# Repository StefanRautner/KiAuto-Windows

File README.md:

KiAuto
======
KiCad automation scripts.
In particular to automate tasks that can't be done using the KiCad native Python interface.
The automation is carried out emulating the user interaction.

## Index

* [Introduction](#introduction)
* [Installation](#installation)
  * [Dependencies](#dependencies)
  * [No installation](#no-installation)
  * [Installation using pip](#installation-using-pip)
  * [Python style installation](#python-style-installation)
  * [Installation on Ubuntu/Debian](#installation-on-debian)
* [Usage](#usage)
  * [Export a schematic to PDF or SVG](#export-a-schematic-to-pdf-or-svg)
  * [Run ERC](#run-erc)
  * [Generate netlist](#generate-netlist)
  * [Update BoM XML or basic BoM generation](#update-bom-xml-or-basic-bom-generation)
  * [Run DRC](#run-drc)
  * [Export layout as PDF](#export-layout-as-pdf)
  * [Refilling copper zones](#refilling-copper-zones)
  * [Common options](#common-options)
  * [Ignoring warnings and errors from ERC or DRC](#ignoring-warnings-and-errors-from-erc-or-drc)
  * [Running on GitLab CI](#running-on-gitlab-ci)
* [History](#history)

## Introduction

Current implementation uses a virtual X server ([xvfb](https://www.x.org/releases/X11R7.6/doc/man/man1/Xvfb.1.xhtml)),
sends key events and detects which window is focused using [xdotool](https://github.com/jordansissel/xdotool/).
This means it works for Linux. KiCad is also available for Windows and MacOSX, help to port the scripts will be appreciated.

Currently tested and working:

- Exporting schematics to PDF, SVG, PS, DXF and HPGL
- Exporting layouts (PCBs) to PDF
- Running ERC on schematics
- Running DRC on layouts
- Netlist generation (including IPC-D-356 format)
- Basic BoM generation (mainly the XML needed for [KiBoM](https://github.com/SchrodingersGat/KiBoM))
- PCB 3D render
- Export PCB in Gencad format
- Export PCB in VRML format

If you are looking for Gerbers, Drill, Position, STEP and more take a look at [KiBot](https://github.com/INTI-CMNB/KiBot).

This project started as a fork of [kicad-automation-scripts](https://github.com/obra/kicad-automation-scripts) for more information read the [history](#History) section.

A docker image containg the scripts and other tools can be found at [DockerHub](https://hub.docker.com/repository/docker/setsoft/kicad_auto).

## Installation

### Dependencies

If you are installing from a Debian package you don't need to worry about dependencies, otherwise you need to install:

- **Python 3.4** or newer
- [**KiCad**](http://kicad.org/) 5.1.x or newer, KiCad 6.x is supported
- [**Xvfb**](https://www.x.org/releases/X11R7.6/doc/man/man1/Xvfb.1.xhtml) This is the X Virtual Frame Buffer, part of X, but usually available as a separated package (i.e. `xvfb`)
- [**xdotool**](https://github.com/jordansissel/xdotool)
- [**xsltproc**](http://xmlsoft.org/xslt/) (usually installed as a KiCad dependency). Only needed for BoMs.
- [**import**](https://imagemagick.org/) from Image Magick. Also provided by Graphics Magick. Only needed for ERC with KiCad 6.
- [**xclip**](https://github.com/astrand/xclip). Only needed by kicad2step_do when using KiCad 6.

The following Python modules are also needed, they are installed by the Debian package and `pip`:

- [**xvfbwrapper**](https://pypi.org/project/xvfbwrapper/)
- [**psutil**](https://pypi.org/project/psutil/)

If you want to debug problems you could also need:

- [**recordmydesktop**](http://recordmydesktop.sourceforge.net/about.php), to create a video of the KiCad session.
- [**x11vnc**](http://www.karlrunge.com/x11vnc/) and a client like [**ssvnc**](http://www.karlrunge.com/x11vnc/ssvnc.html), to see the KiCad live interaction.
- [**fluxbox**](http://fluxbox.org/) and [**wmctrl**](http://tripie.sweb.cz/utils/wmctrl/) if you want to have a window manager when using **x11vnc**. Othewise windows can't be moved.

### Installation using pip

```shell
pip3 install kiauto
```

Note: the `pip` command is usually installed as `pip3` on modern systems. To avoid confusing it with Python 2 version.
You can also install the current git code running:

```shell
pip3 install .
```

In the root of the repo.

### Python style installation

Just run the setup, like with any other Python tool:

```
sudo python3 setup.py install
```

### No installation

You can use the scripts without installing. The scripts are located at the *src/* directory.

You can also define bash aliases:

```
alias pcbnew_do=PATH_TO_REPO/src/pcbnew_do
alias eeschema_do=PATH_TO_REPO/src/eeschema_do
```

Note that the following Python 3 packages must be installed:

- [**xvfbwrapper**](https://pypi.org/project/xvfbwrapper/)
- [**psutil**](https://pypi.org/project/psutil/)

Also note that this won't work if you plan to call the scripts from KiBot or other tool.
Aliases are good for direct command line use, but are restricted to the shell where the aliases are declared.
You can add the aliases to the bash configuration, but if the tool doesn't use bash or don't even use a shell this won't work.

### Installation on Debian

Get the Debian package from the [releases section](https://github.com/INTI-CMNB/KiAuto/releases) and run:
```
sudo apt install ./kiauto_*_all.deb
```

## Usage

Two scripts are provided:

- **eeschema_do**: interacts with KiCad's eeschema (schematic editor)
- **pcbnew_do**: interacts with KiCad's pcbnew (PCB editor)

You can get detailed help using the *--help* command line option. Here I include some basic usage.

### Export a schematic to PDF or SVG

```
eeschema_do export -a YOUR_SCHEMATIC.sch DESTINATION/
```
This will create *DESTINATION/YOUR_SCHEMATIC.pdf* file containing all the schematic pages. If you want just one page remove the *-a* option. If you want an SVG file just use *-f svg* like this:
```
eeschema_do export -a -f svg YOUR_SCHEMATIC.sch DESTINATION/
```
In this case you'll get one SVG for each page in your schematic.

### Run ERC

To run the Electrical Rules Check:
```
eeschema_do run_erc YOUR_SCHEMATIC.sch DESTINATION/
```
If an error is detected you'll get a message and the script will return a negative error level. Additionally you'll get *DESTINATION/YOUR_SCHEMATIC.erc* containing KiCad's report.

### Generate netlist

To generate or update the netlist, needed by other tools:
``` 
eeschema_do netlist YOUR_SCHEMATIC.sch DESTINATION/
```
You'll get *DESTINATION/YOUR_SCHEMATIC.net*

### Update BoM XML or basic BoM generation:

Tools like [KiBoM](https://github.com/SchrodingersGat/KiBoM) can generate a nice BoM, but in order to run them from the command line you need to be sure that the project's XML BoM is updated. You can do it running:
``` 
eeschema_do bom_xml YOUR_SCHEMATIC.sch DESTINATION/
```
After running it *./YOUR_SCHEMATIC.xml* will be updated.

### Run DRC

To run the Distance Rules Check:
```
pcbnew_do run_drc YOUR_PCB.kicad_pcb DESTINATION/
```
If an error is detected you'll get a message and the script will return a negative error level. Additionally you'll get *DESTINATION/drc_result.rpt* containing KiCad's report. You can select the name of the report using *--output_name* and you can ignore unconneted nets using *--ignore_unconnected*.

### Export layout as PDF

This is useful to complement your gerber files including some extra information in the *Dwgs.User* or *Cmts.User* layer.
```
pcbnew_do export YOUR_PCB.kicad_pcb DESTINATION/ LAYER1 LAYER2
```
Will generate *DESTINATION/printed.pdf* containing LAYER1 and LAYER2 overlapped. You can list as many layers as you want. I use things like ```F.Cu Dwgs.User```. The name of the layers is the same you see in the GUI, if your first inner layer is GND you just need to use ```GND.Cu```.

If you need to get a list of valid layers run:

```
pcbnew_do export --list YOUR_PCB.kicad_pcb
```

### Refilling copper zones

When you run the DRC KiCad will refill all zones. If you didn't do it before saving it could lead to a situation where the PCB that passes DRC isn't the one saved to disk. To solve you can use *-s* option to save the PCB after DRC:

```
pcbnew_do run_drc -s YOUR_PCB.kicad_pcb DESTINATION/
```

Another option could be to avoid changing the file on disk, but fill the zones before printing. To achieve it you can invoke the export command like this:

```
pcbnew_do export -f YOUR_PCB.kicad_pcb DESTINATION/ LAYERs...
```

### Common options

By default all the scripts run very quiet. If you want to get some information about what's going on use *-v*. 

The nature of these scripts make them very fragile. In particular when you run them in your every day desktop. You must avoid having *eeschema* and/or *pcbnew* windows opened while running the scripts. If you need to debug a problem you can:
1. Use the *-vv* option to get debug information
2. Use the *-r* option to record a video (OGV format) containing the GUI session. The file will be stored in the output directory and its name will begin with the name of the requested command.
3. Use the *-s* and *-w* options to start **x11vnc**. The execution will stop asking for a keypress. At this time you can start a VNC client like this: ```ssvncviewer :0```. You'll be able to see KiCad running and also interact with it.
4. Same as 3 but also using *-m*, in this case you'll get a window manager to move the windows and other stuff.

### Ignoring warnings and errors from ERC or DRC

Sometimes we need to ignore some warnings and/or errors reported during the ERC and/or DRC test.

To achieve it you need to create a *filters file*. Each line contains a rule to exclude one or more matching errors. The syntax is:

```
ERROR_ID,REGULAR_EXPRESSION
```

The regular expression must follow the Python syntax. In the simplest case this can be just the text that the error must contain.

The error id is just the KiCad internal number for the error you want to ignore. For KiCad 6 this is a string, not a number.

Here is an example, suppose our report says:

```
** Created on 2020-06-05 11:16:21 **

** Found 2 DRC errors **
ErrType(45): Courtyards overlap
    @(144.361 mm, 101.752 mm): Footprint C16 on F.Cu
    @(144.825 mm, 101.244 mm): Footprint C19 on F.Cu
ErrType(45): Courtyards overlap
    @(159.885 mm, 97.663 mm): Footprint R4 on F.Cu
    @(160.393 mm, 97.191 mm): Footprint C21 on F.Cu

** Found 0 unconnected pads **

** End of Report **
```

Here we have two errors, both number 45. So lets suppose we want to ignore the first error, we could use the following filter:

```
45,Footprint C16
```

This will ignore any error of type 45 (Courtyards overlap) related to *Footprint C16*. To use
it you just need mto use the *-f* command line option:

```
pcbnew_do run_drc -f FILTER_FILE YOUR_PCB.kicad_pcb DESTINATION/
```

Note that when using KiCad 6 the errors are strings enclosed by brackets, use only the text, not the brackets.

### Running on GitLab CI

If you want to use KiAuto in GitLab CI servers I'll recommend always using the `-r` option.

The scripts runs very well locally and using GitHub CI servers.
It also worked well on april 25 2020 on GitLab CI.
Tests on august 25 2020 on GitLab CI started to fail.
The v1.5.8 implements a workaround that is working on february 22 2021, but you must enable recording.

In case you are interested the misterious problem is related with the use Xvfb.
After starting Xvfb process we start polling it to ensure the server is up and running.
We use the `setxkbmap -query` command to know if Xvfb finished its start-up and is working.
After we can successfully run `setxkbmap -query` we assume Xvfb is fully functional.
For some reason this isn't true on GitLab CI servers, if we don't wait some time after the test the X server doesn't respond.
What is even more misterious is that we must run `recordmydesktop` or KiCad will fail to initialize GTK+.
I don't have any idea of why, but it works.

## History

I saw a presentation of Jesse Vincent ([@obra](https://github.com/obra)) in the [KiCon 2019](https://2019.kicad-kicon.com/) about automating KiCad tasks.

The presentation used [kicad-automation-scripts](https://github.com/obra/kicad-automation-scripts) as base for the tasks that needs to emulate the user interaction.
So I forked this repo.

But this wasn't the original repo, Jesse's repo is a fork of Productize SPRL's [scripts](https://github.com/productize/kicad-automation-scripts).
These scripts were created by Seppe Stas ([@seppestas](https://github.com/seppestas)).

According to Seppe he took many ideas from the [split-flap display project](https://scottbez1.github.io/splitflap/).
In particular from the files [here](https://github.com/scottbez1/splitflap/tree/master/electronics/scripts).
The author of split-flap is Scott Bezek ([@scottbez1](https://github.com/scottbez1)).
Scott explained the idea in his [blog](https://scottbezek.blogspot.be/2016/04/scripting-kicad-pcbnew-exports.html)

So this is the history of the scripts, at least what I know. In short: Scott Bezek had the original idea and used it for his project, but not as a separated tool.
Seppe Stas from Productize SPRL took the scripts and created a tool from them.
Then Jesse Vincent used the scripts to create a bigger set of tools and presented it on KiCon 2019.
Then Salvador E. Tropea took Jesse's scripts and adapted them to the needs of [KiBot](https://github.com/INTI-CMNB/KiBot).
And Finally I (Stefan Rautner) took the scripts and made a Version that is compatible with Windows.

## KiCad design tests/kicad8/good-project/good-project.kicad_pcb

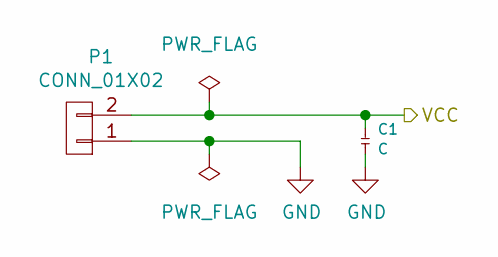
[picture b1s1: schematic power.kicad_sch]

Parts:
C1: C; C_0402_1005Metric
P1: CONN_01X02; JST_JWPF_B02B-JWPF-SK-R_1x02_P2.00mm_Vertical

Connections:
/Power/VCC: C1.1, P1.2; also elsewhere on the board
GND: C1.2, P1.1; also elsewhere on the board

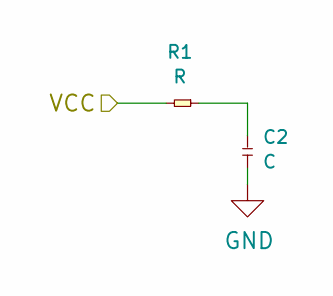
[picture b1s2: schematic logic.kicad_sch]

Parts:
C2: C; C_0402_1005Metric
R1: R; R_0402_1005Metric

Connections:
/Power/VCC: R1.1; also elsewhere on the board
GND: C2.2; also elsewhere on the board
unnamed: C2.1, R1.2

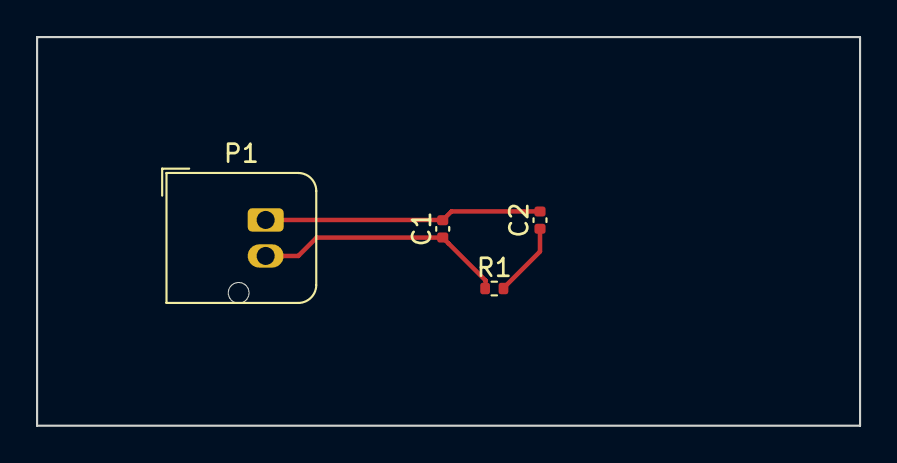
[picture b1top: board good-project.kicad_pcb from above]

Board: 6 copper layers, 45.7 x 21.6 mm, 4 parts (0 on the bottom side), 3 nets.

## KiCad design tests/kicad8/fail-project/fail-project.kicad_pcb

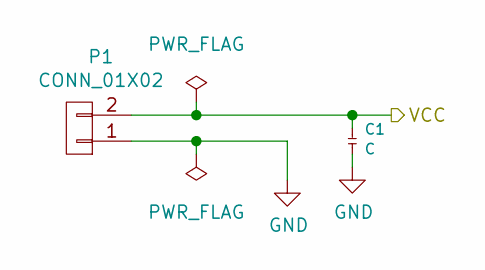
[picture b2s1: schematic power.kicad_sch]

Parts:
C1: C; C_0402_1005Metric
P1: CONN_01X02; JST_JWPF_B02B-JWPF-SK-R_1x02_P2.00mm_Vertical

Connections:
GND: C1.2, P1.1; also elsewhere on the board
VCC: C1.1, P1.2; also elsewhere on the board

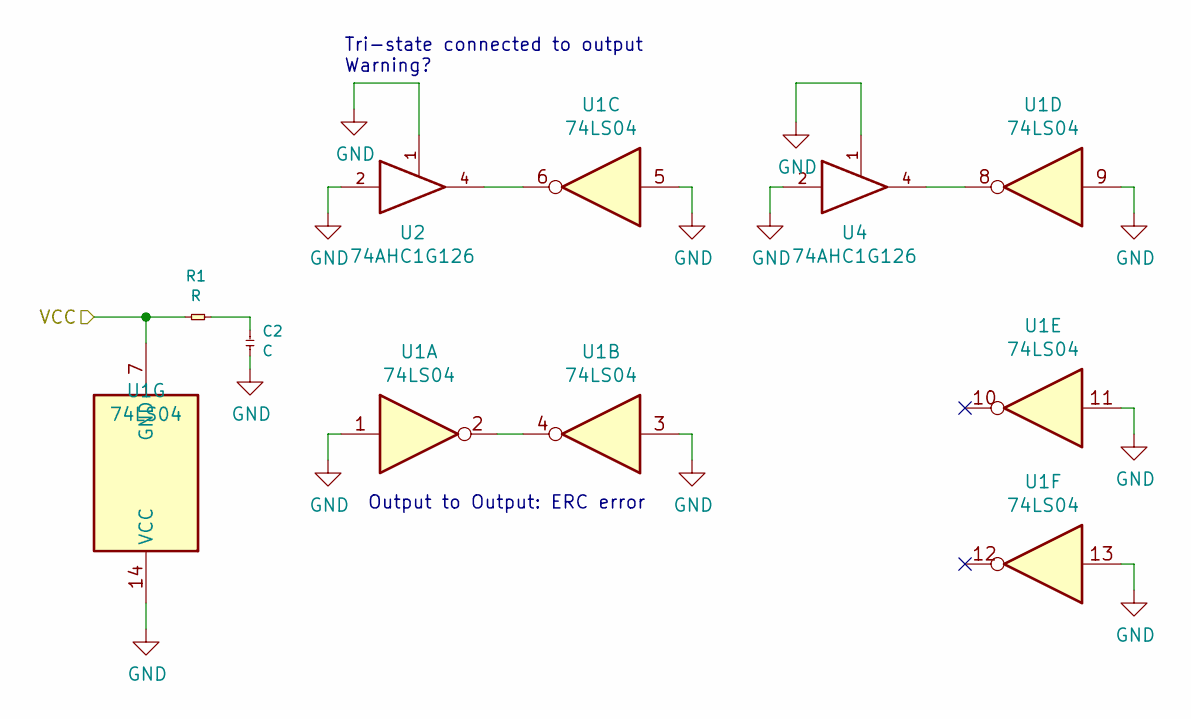
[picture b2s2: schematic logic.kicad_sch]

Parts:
C2: C; C_0402_1005Metric
R1: R; R_0402_1005Metric
U1: 74LS04
U2, U4: 74AHC1G126

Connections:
GND: C2.2, U1.1, U1.3, U1.5, U1.9, U1.11, U1.13, U1.14 (VCC), U2.1, U2.2, U2.3 (GND), U4.1, U4.2, U4.3 (GND); also elsewhere on the board
unnamed: C2.1, R1.2
unnamed: U1.2, U1.4
unnamed: U1.6, U2.4
unnamed: U1.8, U4.4
VCC: R1.1, U1.7 (GND), U2.5 (VCC), U4.5 (VCC); also elsewhere on the board

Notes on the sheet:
Tri-state connected to output Warning?
Output to Output: ERC error

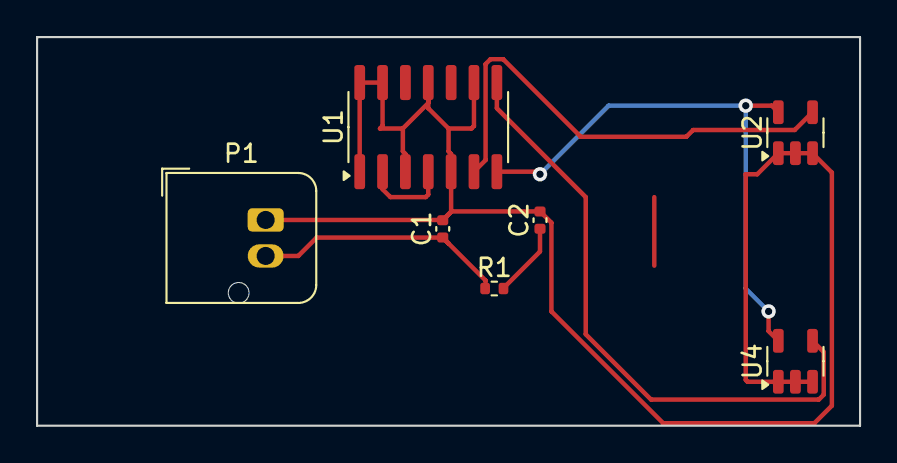
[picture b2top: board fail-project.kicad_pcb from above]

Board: 2 copper layers, 45.7 x 21.6 mm, 7 parts (0 on the bottom side), 6 nets.

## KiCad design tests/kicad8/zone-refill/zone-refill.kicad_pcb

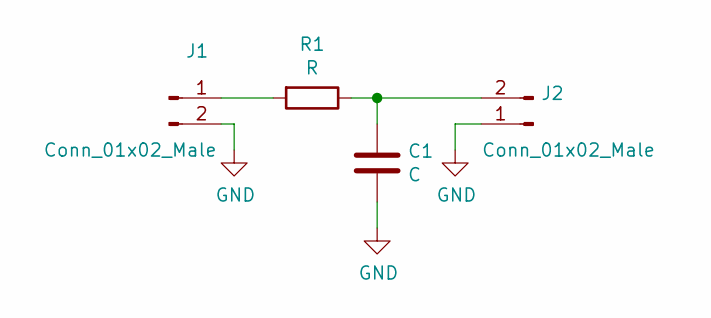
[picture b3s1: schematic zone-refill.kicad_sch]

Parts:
C1: C; C_0805_2012Metric
J1, J2: Conn_01x02_Male; PinHeader_1x02_P2.54mm_Vertical
R1: R; R_0805_2012Metric

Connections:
GND: C1.2, J1.2, J2.1
unnamed: J1.1, R1.2
unnamed: C1.1, J2.2, R1.1

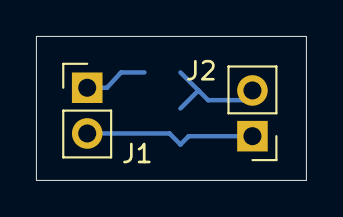
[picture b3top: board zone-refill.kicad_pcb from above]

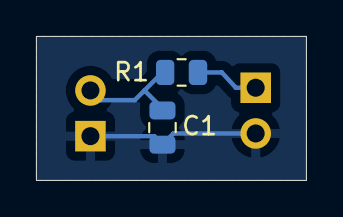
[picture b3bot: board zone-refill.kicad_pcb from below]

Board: 2 copper layers, 15.0 x 8.0 mm, 4 parts (2 on the bottom side), 3 nets.

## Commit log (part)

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2022-10-11 Bumped version to 2.0.6
2022-12-17 Added some preliminar VRML export support
2022-12-17 [Export VRML] Added KiCad 5 support
2022-12-17 [Export VRML] Added some basic tests
    - The file are there ;-)
2022-12-17 Updated changelog
2022-12-17 [CI/CD] Migrated to checkout v3
2022-12-17 Bumped version to 2.1.0
2023-01-11 [Eeschema][Export] Added new options
    - Color theme
    - Enable background color
    - HPGL origin
    - HPGL pen size
    Related to INTI-CMNB/KiBot#362
2023-01-11 [DOCs] Fixed README badge
2023-02-06 [DOCs][Fixed] We no longer generate a CSV as an xml_update side effect
2023-02-07 [ERC] KiCad 7 support
2023-02-07 [Netlist] KiCad 7 support
    - First use of kicad-cli
2023-02-07 [BOM_XML] KiCad 7 support
2023-02-07 [Export] KiCad 7 support
    - All eeschema_do outputs now supports KiCad 7
2023-02-07 [EEschema Export][KiCad 7] Now using the CLI when possible
2023-02-07 [Export GenCAD] KiCad 7 support
    - Works out-of-the-box
2023-02-07 [PCBNew Export] KiCad 7 support
    - Just a small dialog change
2023-02-07 [PCBNew Export] Added note about KiCad 7 bug
2023-02-07 [Render_3D] Added KiCad 7 references
2023-02-08 Replacd nightly version
2023-02-08 [Flake8] Fixed details
2023-02-08 [Interposer] Added support for async dialogs during text paste
2023-02-08 [DRC] KiCad 7 support
    - Python workaround for missing environment variable and fp-lib-table
    Related to a new check for libs
    - New dialog name
    - Adapted the test cases for the new tests
2023-02-08 Fixed missing import symbol
2023-02-08 Fixed flake8 issues
2023-02-08 Fixed 3D models
    - Lost during footprint update done to fix DRC errors
2023-02-08 Adjusted GenCAD reference to KiCad 7 footprints
2023-02-08 Adjusted the references to the KiCad 7 footprints
2023-02-08 Disabled lib_footprint_mismatch (useless)
2023-02-08 Added KiCad 7 support when no interposer is available
2023-02-08 [Iterposer] Avoid waiting for a dialog that is already closed
2023-02-08 [Tests] Trying to enable "nightly" tests
2023-02-08 [Tests] Added missing KiCad 7 "missing-project" files
2023-02-08 Disabling CPU usage detection for KiCad 7, is failing
2023-02-09 Fixed CPU usage detection for nightly
    - It is run from a script, so we need to search for the child
2023-02-14 [Debian] Updated version
2023-02-14 [DOCs] Updated the changelog
2023-02-27 [ERC][Added] Option to select the grid size used for checks
2023-02-27 Bumped version to 2.2.1
2023-02-27 [Tests][Fixed] KiCad version detection
2023-02-27 [Tests] Adjusted the references now that KiCad 7 is fixed
    - Centered scaled print is now working
2023-02-27 [Tests][3D][KiCad 7] Adjusted references
    - Small changes in fonts, may be related to b2241dca72 patch
2023-02-27 Avoid problems when exiting and no interposer dialog
2023-02-27 [Tests][KiCad 7] Adapted references
    - All related to small changes in the font rendering
2023-03-06 Added workaround for KiKit 1.3.0 plugin
2023-03-19 Accept KiCad nightly as dependency
2023-04-02 [Makefile] Added target to run KiCad 7 using docker
2023-04-02 [EEschema] Added support for options in the v8 kicad-cli
2023-04-02 [Tests] Switching to test using KiCad 7 instead of nightly
2023-04-02 [DRC] Added workaround for KiCad 7 DRC API bug
    - No KICAD7* vars defined, KiBot does by itself
2023-04-02 [Makefile] Added local target for all Ki7 docker tests
2023-04-02 [KiCad 7] Updated references
2023-04-02 [Tests] Let the parallel jobs to finish if one fails.
2023-04-02 [Tests] Fixed faiñ-fast position
2023-04-02 [Tests] Trying without continu-on-error
2023-04-06 [Tests] Added auto save test files
2023-04-06 Added support for KICad async warnings
    - Missing font generates it
2023-04-06 Bumped version to 2.2.3
2023-04-12 Added better debug for global fp/sym-lib-table issues
2023-04-12 Added share directory detection
    - Also more consistent version flags
2023-04-12 [Eeschema_do][Added] Support for v7.99 ERC
    - Dialog not closed
    - File name forced by KiCad
2023-04-12 [KiCad 8][Added] Test and reference files
    - For 7.99
2023-04-12 [Tests][KiCad 7] Removed no longer needed fp-lib-table
    - 7.0.1 fixes it (7.99 don't)
2023-04-12 [Interposer][Added][KiCad 8] Support
    - ERC dialog not really closed
    - File names forced by KiCad
    - Async dialogs in send_keys (missing WKS)
2023-04-12 [Tests][Added] Targets to the Makefile
    - KiCad 7.99
2023-04-12 Bumped version to 2.2.4
2023-04-17 [Tests][good][KiCad 7] Adapted to the new ERC errors in 7.0.2
2023-04-17 [Eeschema][KiCad 7.0.2][Added] Workaround for ERC
    - Workaround for bogus KiCad 7.0.2 error about missing simulation model for
    power symbols.
2023-04-17 [Eeschema][KiCad 7.0.2][Added] Workaround for ERC dialog
    - Closes after running the ERC.
2023-04-17 [Eeschema] Better error/warning formating
2023-04-17 [Tests][KiCad 7] Ignore silk clipped by solder mask
2023-04-17 [Tests][References] Updated for the last changes
    - Mostly because I fixed some out-off-grid errors
2023-04-17 [Eeschema][ERC][KiCad 7][No interposer] Added workaround
2023-04-18 [Makefile] Switching to ki7 by default
2023-04-18 Bumped version to 2.2.5
2023-04-18 [3D] Added more delay to KiCad 5
2023-04-18 [KiCad2Step][Added] Support for the broken version in 7.99
    - The old --no-virtual was renamed to be more coherent, but breaking old code
    KiCad favors clarity over compatibility, and rarely both together.
2023-04-20 Changed shortcut for E/DRC
    - Ctrl+Shift+I is interpreted as Ctrl+Shift+^I, which is Ctrl+Shift+Tab,
    which is reserved by KiCad.
2023-04-20 [ERC] Added another 7.99 workaround
    - This dialog is crazy
2023-06-08 Bumped version to 2.2.6
    - Just to avoid confusion
2023-06-08 [Added][3d_view] More options to control the result
    - use_layer_colors: instead of realistic
    - hide_board_body: transparent core
    - show_comments: visible User.Comments (only when use_layer_colors enabled)
    - show_eco: visible Eco*.User (only when use_layer_colors enabled)
    - show_adhesive: visible *.Adhesive
    See INTI-CMNB/KiBot#445
2023-06-09 [Tests] KiCad 7.0.5 no longer specify the unit for an ERC error
    - So I made this filter more generic
2023-06-09 [Fixed] Problems with KiCad 7.0.5 ERC formatting
2023-06-09 [Tests][References][KiCad 7.0.5] Updated
2023-06-12 Updated docs for release
2023-08-08 Added support for KiCad 7.0.7 already opened dialog
    It adds more information about the user and host that locked the file
2023-08-08 Added support for KiCad 7.0.7 gencad dialog
    Without a Window Manager selecting the first checkbox and going up
    doesn't select the input text, the Browse button is selected.
2023-08-08 Added support for KiCad 7.0.7 ERC dialog behavior
    No longer closed by ESC, but we can use the patched button.
2023-08-08 Added stable nightly test
2023-08-08 Fixed stable nightly workflow deps
2023-08-08 Fixed stable nightly docker image name
2023-08-08 [Tests] Stable nightly test only manually triggered
    - Currently fails because of small details in KiCad PCB print
2023-08-08 [Tests] Updated the stable nightly used actions
2023-08-08 Bumped version to 2.2.7
2023-10-12 [Added][Experimental] Option to enable the file creation by PID
    When using the interposer.
    Related to INTI-CMNB/KiBot#367
2023-10-12 [Tests] Adjusted KiCad 7.0.8 references
2023-10-12 [Added] Support for KiCad 7.0.8 ERC details
2023-10-12 [Makefile][Added] Target for KiCad 6 + no interposer test
2023-10-12 [Tests][Added] More toletance to rendered images
2023-10-12 [ERC][Fixed] Error introduced in the 7.0.8 support
    Extra return
2023-10-12 [Fixed][KiCad 7.0.8] PCB print dialog
    When no interposer, the Print/Close buttons are moved
2023-10-12 [Fixed][KiCad 6][Eeschema][Plot] More robust
    Force buttons selection in a more robust way
2023-10-13 [Print][PCB][Fixed][No Interposer] Debian 12 issues
2023-10-13 [DRC][No Interposer][Fixed] Debian 12 issues
2023-10-22 [CI/CD] Build all images after a release
    But don't run the KiBot release tests, should be dev (not available)
2023-10-23 [Interposer] Look for architecture specific file
2023-11-02 [Fixed] Removed debug "error" from kicad2step_do
    Closes #34
2023-11-08 [Interposer][Experimental] Added fclose64 and close64
    - They doesn't exist on amd64, but perhaps they do on ARM64
2023-11-24 [flake8][Fixed] Small style details
2023-11-24 [Interposer] Compiled with Debian 11
    To make it compatible with KiCad 5
2023-11-24 Forced test
2024-02-02 [Tests] Adjusted GenCAD ref for KiCad 7.0.10
    The board edge is generated in the reverse order.
    Same result, different rotation of the points
2024-02-02 [Tests][CI/CD] Updated GitHub Actions versions
2024-02-09 [ERC][KiCad 8][Added] Support for CLI
    Lamentably affected by bugs, so still parsing text, which is even weaker
    because they removed the "Severity" keyword
2024-02-16 [Added][KiCad 8] Workaround for bogus lock message
2024-02-16 [PCBNew][DRC] Implemented CLI version
2024-02-16 [EEschema][ERC] Implemented kicad-cli JSON parser
2024-02-16 [PCBNew][DRC][Added][KiCad 8] More options
    - '--schematic-parity'/'-p' Check PCB vs SCH parity
    - '--all-track-errors'/'-t' Report all errors for each track
    - '--units'/'-u' Report units
2024-02-17 [KiCad 8][3D Render] Adapted tests
    - Also removed the layer manager panel
2024-02-17 [PCBNew][DRC][Fixed] Main error description
    We got the last item description
2024-03-20 [KiCad 8][Added] Support for already open dialog
    Now uses the absolute path to the file
2024-03-20 [KiCad 8][EEschema][Export] Filtered some options
    Not all formats supports all command line options
2024-03-20 [KiCad 8][Fixed] Render child process exits
    - When not using the interporser
    - The child process used to render is destroyed after rendering
2024-03-20 [Tests][KiCad 8] Adapted
    - Different error and no time-out
2024-03-20 [Fixed][flake8] Indentation issue
2024-03-20 [Tests][Changed] More robust about transparency
    KiCad isn't fully coherent on this
2024-03-20 [KiCad 8] Migrated test cases
    Some of them remained in KiCad 7 format
2024-03-20 [Tests][References][KiCad 8] Updated
    To the current docker images and 8.0.1
2024-03-20 [Makefile][KiCad 8][Added] test targets
2024-03-20 [CI/CD][Tests][Added][KiCad 8] Experimental test
2024-03-20 [Tests][Added] Some tolerance (transparency issue)
2024-03-20 [Makefile][CI/CD][Tests][Fixed][KiCad 8] Missing target
2024-03-20 [CI/CD] Trying to upload coverage using the GHA
2024-03-21 [EEschema][KiCad 8] Implemented 1 page plot
2024-03-21 [EEschema][Export][KiCad 8] Implemented HPGL options
    Also documented some exceptions
2024-03-21 Bumped version to 2.3.0
2024-03-21 [Setup][Fixed] Package discovery
2024-03-21 [CI/CD][Added] Trigger KiCad 8 images after release
2024-04-02 Avoid messing with config file when using Python/CLI
    - Saves time and problems
    - Could be a workaround for Windows issues (INTI-CMNB/KiBot#599)
2024-04-02 [Tests] Ajusted
    - KiCad 8 uses CLI, no back-ups for eeschema_do
    - Using ipc_netlist for PCB bkps, always from GUI
2024-04-02 [Fixed] We must check the config dir before lib tables
2024-04-22 [3D Render] Various options to control extra text
    - KiCad 8:
    - User drawings
    - User Eco 1
    - User Eco 2
    - Not realistic
    - KiCad 5:
2024-04-23 [CI/CD] Try using coveralls reporter 0.6.9
    - 0.6.10, currently used by the GHA breaks Python support
2024-04-23 [Fixed] Missing defaults for non 3D render
2024-04-23 [CI/CD] No "coverage" file here
2024-04-23 [Tests][Added] Tests for the comments/drawings in 3D
    - Note how different KiCad versions behave really different
2024-04-23 Updated version info for release
2024-04-23 [Tests] Adjusted KiCad 7 reference
    Difference between docker image and local system
2024-05-29 Bumped version to 2.3.2
    To avoid confusion
2024-05-29 [PCBNew][Added] Option to convert foreign PCBs
    Experimental, works for an Altium file I got as reference
2024-06-19 [Added] Support for KiCad 8.0.3
    Which creates a bogus window called "Report" at start-up
2024-06-19 [Tests][Reference] Adjusted for KiCad 8.0.3
2024-08-13 Upload Windows support
2024-08-13 Move ui_automation.py to kiauto/ui_automation.py
